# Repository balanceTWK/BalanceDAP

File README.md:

# BalanceDAP

本项目长期偶尔更新！如有疑问，请[邮箱](mailto:balancetwk@yeah.net)联系我。balanceTWK@yeah.net

代码工程：基于开源免费的 [DAPLink](https://github.com/ARMmbed/DAPLink), [RT-Thread](https://github.com/RT-Thread/rt-thread),

电路板工程：使用开源免费的 [KiCad](http://docs.kicad-pcb.org/) 构建。

本仓库同样开源免费，遵守 [Apache License 2.0 协议](./LICENSE).

## 电路板效果图

## 移植成 rt-thread 后的效果：

## 问题汇总：

 1. 关于使用 KiCad 打开工程出现原理图缺失元器件的问题：原因是没有安装和作者相同的 KiCad 库，请到此 [链接](https://github.com/balanceTWK/lc_kicad_lib)  处下载。

 2. 关于 MDK 不识别 CMSIS-DAP V2 的问题：参考 /doc 目录下 [Notes.md](doc/Notes.md)。

 ## 感谢：

[@Guozhanxin](https://github.com/Guozhanxin)

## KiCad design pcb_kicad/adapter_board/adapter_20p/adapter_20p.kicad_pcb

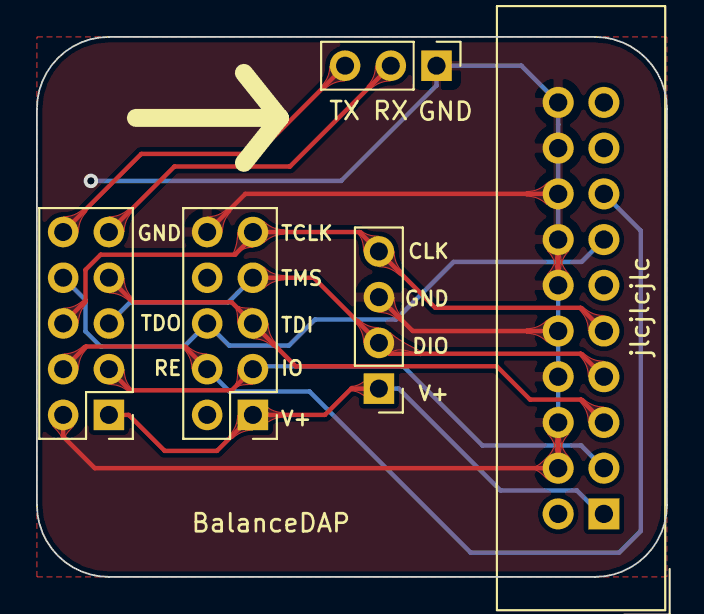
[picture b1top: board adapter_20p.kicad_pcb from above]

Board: 2 copper layers, 35.0 x 30.0 mm, 5 parts (0 on the bottom side), 10 nets.

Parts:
J1, J4: Conn_02x05_Top_Bottom; PinHeader_2x05_P2.54mm_Vertical
J2: Conn_02x10_Top_Bottom; IDC-Header_2x10_P2.54mm_Vertical
J3: Conn_01x03; PinHeader_1x03_P2.54mm_Vertical
J5: Conn_01x04; PinHeader_1x04_P2.54mm_Vertical

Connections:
/IO: J1.3, J2.3, J4.3
/RESET: J1.4, J2.15, J4.4
/TCLK\SWCLK: J1.6, J2.9, J4.9, J5.4
/TDI: J1.7, J2.5, J4.5
/TDO: J1.8, J2.13, J4.6
/TMS\SWDIO: J1.5, J2.7, J4.7, J5.2
/UART_RX: J1.9, J3.2
/UART_TX: J1.10, J3.3
/VREF+: J1.1, J2.1, J4.1, J5.1
GND: J1.2, J2.4, J2.6, J2.8, J2.10, J2.12, J2.14, J2.16, J2.18, J2.20, J3.1, J4.10, J5.3

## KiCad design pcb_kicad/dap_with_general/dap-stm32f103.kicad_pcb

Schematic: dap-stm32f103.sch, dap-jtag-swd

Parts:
C1, C2: 0402_22pF__220_5%_50V; 0402_C
C3, C4, C5, C8, C11, C12, C13, C14, C15: 0402_100nF__104_10%_16V; 0402_C
C6, C10: 0603_10uF__106_10%_10V; 0603_C
D1: LED_RCBG; LED_D5.0mm-4_RGB
J1: USB_C_Receptacle_USB2.0; USB_C_Receptacle_Palconn_UTC16-G
J2: Conn_02x05_Top_Bottom; PinHeader_2x05_P2.54mm_Vertical
J3: Conn_01x09; PinHeader_1x09_P2.54mm_Vertical
J4: Conn_01x06; PinHeader_1x06_P2.54mm_Vertical
R1, R2, R4, R5: 0402_10KΩ__1002_1%; 0402_R
R3: 0402_100KΩ__1003_1%; 0402_R
R6: 0402_100Ω__1000_1%; 0402_R
R7, R8: 0402_5.1KΩ__5101_1%; 0402_R
R9, R10, R11, R12: 0402_510Ω__5100_1%; 0402_R
R13: 0402_1.5KΩ__1501_1%; 0402_R
R14, R15: 0402_22Ω__22R0_1%; 0402_R
R16: 0402_0Ω__0R0_1%; 0402_R
SW1: SW_Push; SW_Tactile_SPST_Angled_PTS645Vx58-2LFS
U1: W25Q128FVSIG_[C35101]; SOIC-8_208MIL
U2: STM32F103CBTx; LQFP-48_7x7mm_P0.5mm
VR1: SOT-223_AMS1117-3.3; SOT-223
Y1: SMD-5032_2P_8MHz_20ppm_20pF; SMD-5032_2P

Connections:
+3V3: C5.1, C10.1, C11.1, C12.1, C13.1, C14.1, C15.1, D1.2, J2.1, J4.1, R1.1, R5.1, R16.2, SW1.2, U1.3, U1.7, U1.8, U2.1 (VBAT), U2.9 (VDDA), U2.24 (VDD), U2.36 (VDD), U2.48 (VDD), VR1.2
+5V: C6.1, C8.1, J1.A4, J1.A9, J1.B4, J1.B9, VR1.3
/IF_NRESET: C4.2, R5.2, U2.7 (NRST)
/IF_SWCLK: J4.4, U2.37 (PA14)
/IF_SWDIO: J4.2, U2.34 (PA13)
/IF_UART_RX: J4.5, U2.31 (PA10)
/IF_UART_TX: J4.6, U2.30 (PA9)
/MCU_USB_D+: R15.1, U2.33 (PA12)
/MCU_USB_D-: R14.1, U2.32 (PA11)
/PA0: R9.1, U2.10 (PA0)
/PA1: J3.8, U2.11 (PA1)
/PA8: J3.3, U2.29 (PA8)
/PB6: R13.2, R16.1, U2.42 (PB6)
/PB7: R11.2, U2.43 (PB7)
/PB8: R12.2, U2.45 (PB8)
/PB9: R10.2, U2.46 (PB9)
/PB10: J2.2, U2.21 (PB10)
/PB11: J3.9, U2.22 (PB11)
/PB12: J3.7, U2.25 (PB12)
/PB13: J3.6, U2.26 (PB13)
/PB14: J3.5, U2.27 (PB14)
/PB15: J3.4, U2.28 (PB15)
/PC14: J3.1, U2.3 (PC14)
/PC15: J3.2, U2.4 (PC15)
/SPI_MISO: U1.2, U2.40 (PB4)
/SPI_MOSI: U1.5, U2.41 (PB5)
/SPI_SCK: U1.6, U2.39 (PB3)
/STAMP_TCLK\SWCLK: J2.8, U2.16 (PA6)
/STAMP_TDI: J2.4, U2.15 (PA5)
/STAMP_TDO: J2.9, U2.14 (PA4)
/STAMP_TMS\SWDIO: J2.3, R6.2, U2.18 (PB0)
/STAMP_UART_RX: J2.5, U2.13 (PA3)
/STAMP_UART_TX: J2.10, U2.12 (PA2)
/STAMP_nSRESET: C3.1, J2.7, R1.2, U2.19 (PB1)
/TGT_USB_D+: J1.A6, J1.B6, R13.1, R15.2
/TGT_USB_D-: J1.A7, J1.B7, R14.2
/W25Q_CS: U1.1, U2.38 (PA15)
GND: C1.1, C2.1, C3.2, C4.1, C5.2, C6.2, C8.2, C10.2, C11.2, C12.2, C13.2, C14.2, C15.2, J1.A1, J1.A12, J1.B1, J1.B12, J1.S1, J2.6, J4.3, R2.2, R3.1, R4.1, R7.2, R8.2, U1.4, U2.8 (VSSA), U2.23 (VSS), U2.35 (VSS), U2.47 (VSS), VR1.1
unnamed: C1.2, U2.6 (PD1), Y1.1 (OSC1)
unnamed: C2.2, U2.5 (PD0), Y1.2 (OSC2)
unnamed: D1.1, R10.1
unnamed: D1.3, R12.1
unnamed: D1.4, R11.1
unnamed: J1.A5, R7.1
unnamed: J1.B5, R8.1
unnamed: R2.1, U2.20 (PB2)
unnamed: R3.2, U2.44 (BOOT0)
unnamed: R4.2, U2.2 (PC13)
unnamed: R6.1, U2.17 (PA7)
unnamed: R9.2, SW1.1

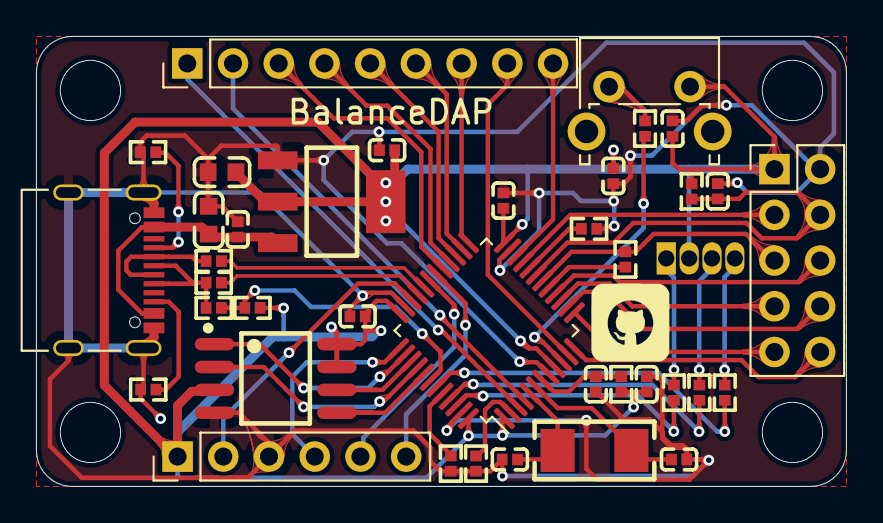
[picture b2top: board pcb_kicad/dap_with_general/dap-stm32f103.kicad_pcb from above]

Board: 2 copper layers, 45.0 x 25.0 mm, 39 parts (1 on the bottom side), 50 nets.

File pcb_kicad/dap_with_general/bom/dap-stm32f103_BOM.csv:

"Comment","Description","Designator","Footprint","LibRef","Pins","Quantity","PartNumber","url",
"0402_100nF__104_10%_16V","desc","C11,C4,C12,C13,C3,C14,C15,C5,C8,","0402_C","libref","2","9","","",
"0402_22pF__220_5%_50V","desc","C2,C1,","0402_C","libref","2","2","","",
"0603_10uF__106_10%_10V","desc","C6,C10,","0603_C","libref","2","2","","",
"LOGO","desc","G***,","github","libref","0","1","","",
"0402_510Ω__5100_1%","desc","R10,R11,R12,R9,","0402_R","libref","2","4","","",
"0402_1.5KΩ__1501_1%","desc","R13,","0402_R","libref","2","1","","",
"0402_22Ω__22R0_1%","desc","R14,R15,","0402_R","libref","2","2","","",
"0402_0Ω__0R0_1%","desc","R16,","0402_R","libref","2","1","","",
"0402_100KΩ__1003_1%","desc","R3,","0402_R","libref","2","1","","",
"0402_10KΩ__1002_1%","desc","R5,R4,R2,R1,","0402_R","libref","2","4","","",
"0402_100Ω__1000_1%","desc","R6,","0402_R","libref","2","1","","",
"0402_5.1KΩ__5101_1%","desc","R8,R7,","0402_R","libref","2","2","","",
"W25Q128FVSIG_[C35101]","desc","U1,","SOIC-8_208MIL","libref","8","1","","",
"STM32F103CBTx","desc","U2,","LQFP-48_7x7mm_P0.5mm","libref","48","1","","",
"SOT-223_AMS1117-3.3","desc","VR1,","SOT-223","libref","4","1","","",
"SMD-5032_2P_8MHz_20ppm_20pF","desc","Y1,","SMD-5032_2P","libref","2","1","","",
"Through Hole Items ",
"USB_C_Receptacle_USB2.0","desc","J1,","USB_C_Receptacle_Palconn_UTC16-G","libref","22","1","","",
"Conn_02x05_Top_Bottom","desc","J2,","PinHeader_2x05_P2.54mm_Vertical","libref","10","1","","",
"Conn_01x09","desc","J3,","PinHeader_1x09_P2.54mm_Vertical","libref","9","1","","",
"Conn_01x06","desc","J4,","PinHeader_1x06_P2.54mm_Vertical","libref","6","1","","",
"SW_Push","desc","SW1,","SW_Tactile_SPST_Angled_PTS645Vx58-2LFS","libref","4","1","","",
"LED_RCBG","desc","D1,","LED_D5.0mm-4_RGB","libref","4","1","","",

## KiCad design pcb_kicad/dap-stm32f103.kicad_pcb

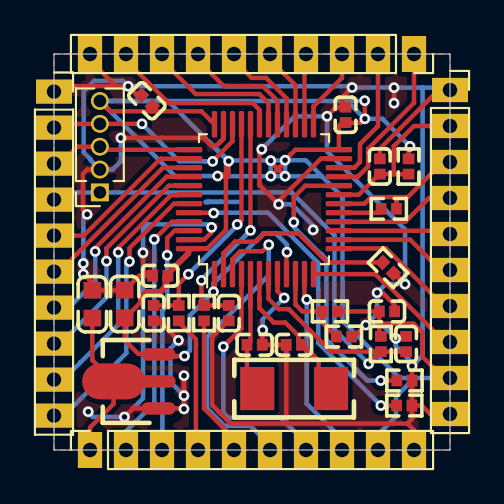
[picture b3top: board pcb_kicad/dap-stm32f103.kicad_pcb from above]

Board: 2 copper layers, 22.0 x 22.0 mm, 30 parts (0 on the bottom side), 44 nets.

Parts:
C1, C2: 0402_22pF__220_5%_50V; 0402_C
C3, C4, C11, C12, C13, C14: 0402_100nF__104_10%_16V; 0402_C
C5, C7: 0603_10uF__106_10%_10V; 0603_C
C6, C8: 0402_18pF__180_5%_50V; 0402_C
IF_SWD1: Conn_01x05; PinSocket_1x05_P1.27mm_Vertical
J1, J2, J3, J4: Conn_01x10; stamp_2.0mm_1x10
R1, R2, R7: 0402_10KΩ__1002_1%; 0402_R
R5: 0402_100Ω__1000_1%; 0402_R
R6, R8: 0402_100KΩ__1003_1%; 0402_R
R9, R10: 0402_4.7KΩ__4701_1%; 0402_R
R11, R12: 0402_33Ω__33R0_1%; 0402_R
U1: STM32F103CBTx; LQFP-48_7x7mm_P0.5mm
VR1: SOT-89_HT7533-1; SOT-89(SOT-89-3)
Y1: SMD-5032_2P_8MHz_20ppm_20pF; SMD-5032_2P

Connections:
+3V3: C7.1, C11.1, C12.1, C13.1, C14.1, IF_SWD1.5, J2.9, J4.9, R1.1, R8.1, R9.1, U1.1, U1.9, U1.24, U1.36, U1.48, VR1.3
+5V: C5.1, J4.1, VR1.2
/IF_NRESET: C3.2, IF_SWD1.1, J1.4, R8.2, U1.7
/IF_SWCLK: IF_SWD1.3, J1.3, U1.37
/IF_SWDIO: IF_SWD1.4, J1.2, U1.34
/PA1: J4.8, U1.11
/PA8: J3.7, U1.29
/PA9: J3.8, U1.30
/PA10: J3.9, U1.31
/PA15: J1.5, U1.38
/PB3: J1.6, U1.39
/PB4: J1.7, U1.40
/PB5: J1.8, U1.41
/PB6: J1.9, U1.42
/PB7: J1.10, U1.43
/PB8: J4.2, U1.45
/PB9: J4.3, U1.46
/PB10: J3.1, U1.21
/PB11: J3.2, U1.22
/PB12: J3.3, U1.25
/PB13: J3.4, U1.26
/PB14: J3.5, U1.27
/PB15: J3.6, U1.28
/PC14: J4.6, U1.3
/PC15: J4.7, U1.4
/STAMP_TCLK\SWCLK: J2.4, U1.16
/STAMP_TDI: J2.5, U1.15
/STAMP_TDO: J2.6, U1.14
/STAMP_TMS\SWDIO: J2.3, R5.2, U1.18
/STAMP_UART_RX: J2.8, U1.12
/STAMP_UART_TX: J2.7, U1.13
/STAMP_nSRESET: C4.1, J2.2, R1.2, U1.19
/TGT_USB_D+: J4.5, R11.2
/TGT_USB_D-: J4.4, R12.2
GND: C1.1, C2.1, C3.1, C4.2, C5.2, C6.2, C7.2, C8.2, C11.2, C12.2, C13.2, C14.2, IF_SWD1.2, J1.1, J2.1, J2.10, J3.10, J4.10, R2.2, R6.1, R7.1, R10.2, U1.8, U1.23, U1.35, U1.47, VR1.1
unnamed: C1.2, U1.6, Y1.1
unnamed: C2.2, U1.5, Y1.2
unnamed: C6.1, R11.1, U1.32
unnamed: C8.1, R12.1, U1.33
unnamed: R2.1, U1.20
unnamed: R5.1, U1.17
unnamed: R6.2, U1.44
unnamed: R7.2, U1.2
unnamed: R9.2, R10.1, U1.10

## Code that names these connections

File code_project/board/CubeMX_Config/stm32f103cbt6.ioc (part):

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Mcu.Name=STM32F103C(8-B)Tx
Mcu.Package=LQFP48
Mcu.UserName=STM32F103CBTx
PA10.Mode=Asynchronous
PA10.Signal=USART1_RX
PA11.Mode=Device
PA11.Signal=USB_DM
PA12.Mode=Device
PA12.Signal=USB_DP
PA13.Mode=Serial_Wire
PA13.Signal=SYS_JTMS-SWDIO
PA14.Mode=Serial_Wire
PA14.Signal=SYS_JTCK-SWCLK
PA9.Mode=Asynchronous
PA9.Signal=USART1_TX
PB3.Mode=Full_Duplex_Master
PB3.Signal=SPI1_SCK
PB4.Mode=Full_Duplex_Master
PB4.Signal=SPI1_MISO
PB5.Mode=Full_Duplex_Master
PB5.Signal=SPI1_MOSI
PD0-OSC_IN.Mode=HSE-External-Oscillator
PD0-OSC_IN.Signal=RCC_OSC_IN
PD1-OSC_OUT.Mode=HSE-External-Oscillator
PD1-OSC_OUT.Signal=RCC_OSC_OUT
RCC.SYSCLKFreq_VALUE=72000000
RCC.SYSCLKSource=RCC_SYSCLKSOURCE_PLLCLK
board=custom

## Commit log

2019-10-05 [first] pcb project
2019-10-09 [update] pcb
2019-10-10 [update] pcb sch
2019-10-13 [update] SCH
2019-10-15 [update] SCH done
2019-10-19 [pcb] 20%
2019-10-20 [update] pcb 25%
2019-10-21 [update] pcb 连线完成
2019-10-21 [pcb] done
2019-10-27 [update] stamp footprint
2019-10-29 [done] stamp pcb
2019-10-31 [delete] Useless files
2019-11-01 [update] Gerber files
2019-11-02 [update] directory
2019-11-02 [init] pcb general
2019-11-08 [update] pcb general
2019-11-09 [update] pcb general gerber
2019-11-09 [update] pcb general readme.md
2019-11-10 Create LICENSE
2019-11-11 [first] add code_project
2019-11-11 [optimize] Reduce the size of the bin file generated by MDK
2019-11-11 [update] rtconfig.h
2019-11-11 [add] DAPLink source code ,Not compiled.
2019-11-13 [update] LICENSE
2019-11-13 [first add] rtthread port files
2019-11-13 [update] rtthread port files
2019-11-15 [Delete] useless files
2019-11-15 [update] DAPLink/LICENSE
2019-11-15 [add] dap_with_general/bom/*.csv
2019-11-15 [delete] cmsis rtos2 port files
2019-11-15 [add] package: CMSIS-v5.0.0/RTOS2
2019-11-17 [update] DAPLink SConscript
2019-11-17 [update] README
2019-11-19 [update] pcb_kicad/dap_with_general
2019-11-19 [update] bom/dap-stm32f103_POS.csv
2019-11-21 [update] SWD pin number
2019-11-21 [add] dap_with_general.pdf
2019-11-22 [add] picture/DAPLink_learn1.jpg
2019-11-23 [sync] gcc : https://github.com/flit/DAPLink/tree/feature/gcc
2019-11-23 [add] usb
2019-11-24 [add] FLAGS_MAIN_PROC_USB.jpg
2019-11-30 [delete] stamp pcb
2019-11-30 [update] BOM and POS
2019-12-01 [update] dap_with_general.pdf
2019-12-01 [update] README.md
2019-12-05 [update] usb connect pin
2019-12-08 [update] DAPLink IO and DAPLINK_ROM_IF_START
2019-12-08 添加注意事项文档。
2020-02-01 [update] CubeMX_Config : spi and rtc
2020-02-01 [add] spi flash
2020-02-01 [update] CubeMX_Config
2020-02-02 [update] directory
2020-02-02 [add] rtos/rt-thread-3.1.3/
2020-02-02 [add] packages/CMSIS-v5.0.0
2020-02-02 [change] RTX --> rt-thread,!!!but only led runing.
2020-02-03 [update] rt-thread os is ok,but daplink not adaptive!
2020-02-03 [update] rt_system_heap_init((void *)HEAP_BEGIN, (void *)HEAP_END);
2020-02-03 [BUG] osThreadFlagsSet:rt_thread_resume(rt_thread_self()); -> rt_thread_resume(&thread_cb->thread);
2020-02-04 [tag] update osThreadFlagsxxx; TEST OK！
2020-02-16 [del] Delete irrelevant project directory
2020-02-16 [code] Reduce bin file size.
2020-02-16 [update] code_project
2020-02-16 [update] Change engineering structure
2020-02-19 [code_project] Add rt-thread device framework support.1. Add uart drivers.2. Add spi flash driver and components.3. Add the finsh component.
2020-02-23 [add] SCons function.
2020-02-23 [delete] RTE/_stm32f103xb_if/RTE_Components.h
2020-02-25 [first try] gcc
2020-02-29 [add] pcb adapter
2020-03-04 添加 littlefs 支持
2020-03-06 `vallen` is verified to be less than `len`, therefore, it can never be the case that `vallen >= len + sizeof(rhostname)`.
    This PR fixes the check so the `rhostname` array does not overflow.
    Reported-by: Github Security Lab <securitylab@github.com>
2020-03-08 [change] #define _MSH_PROMPT "msh " -> #define _MSH_PROMPT "BalanceDAP@MSH "
2020-03-15 [first add] FreeCAD
2020-03-21 将 hal 库移到外部
2020-03-21 将port部分抽离出来
2020-03-21 使用官方 stm32 hal 库
2020-03-21 还原启动文件修改
2020-03-29 [FreeCAD] BalanceDAP.FCStd
2020-03-29 [code_project] update project directory structure
